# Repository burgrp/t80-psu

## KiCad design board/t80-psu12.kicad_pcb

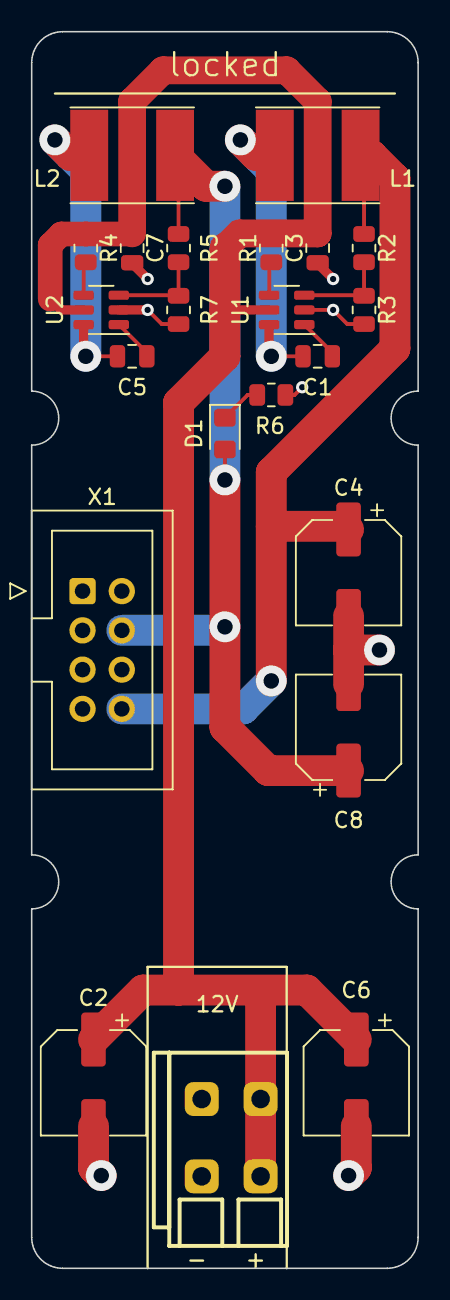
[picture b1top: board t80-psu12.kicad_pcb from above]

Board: 2 copper layers, 25.0 x 80.0 mm, 22 parts (0 on the bottom side), 13 nets.

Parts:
C1, C3, C5, C7: 100n; C_0805_2012Metric
C2, C4, C6, C8: 100u/12V; CP_Elec_6.3x5.4
D1: WHITE; LED_0805_2012Metric_Pad1.15x1.40mm_HandSolder
J1: Conn_01x02_Female; DG235-3.81-02P
L1, L2: 6.8uH; CKCS6028
R1, R4: 100k; R_0805_2012Metric
R2: 30.9k 1%; R_0805_2012Metric
R3: 4.22k 1%; R_0805_2012Metric
R5: 30k 1%; R_0805_2012Metric
R6: 1k5; R_0805_2012Metric
R7: 6.65k 1%; R_0805_2012Metric
U1, U2: FR8205; SOT-23-6
X1: IDC-Header_2x04_P2.54mm_Vertical

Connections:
+3V3: C8.1, D1.2 (A), L2.2, R5.2, X1.4 (3V3)
+5V: C4.1, L1.2, R2.2, X1.8 (5V)
+12V: C2.1, C3.2, C6.1, C7.2, J1.2, R1.2, R4.2, U1.5 (VIN), U2.5 (VIN)
GND: C2.2, C3.1, C4.2, C6.2, C7.1, C8.2, J1.1, R3.1, R6.2, R7.1, U1.2 (GND), U2.2 (GND), X1.1 (GND), X1.7 (GND)
unnamed: D1.1 (K), R6.1
unnamed: C1.1, U1.1 (BST)
unnamed: R2.1, R3.2, U1.3 (FB)
unnamed: C1.2, L1.1, U1.6 (LX)
unnamed: R1.1, U1.4 (SHDN)
unnamed: C5.1, U2.1 (BST)
unnamed: R5.1, R7.2, U2.3 (FB)
unnamed: C5.2, L2.1, U2.6 (LX)
unnamed: R4.1, U2.4 (SHDN)
